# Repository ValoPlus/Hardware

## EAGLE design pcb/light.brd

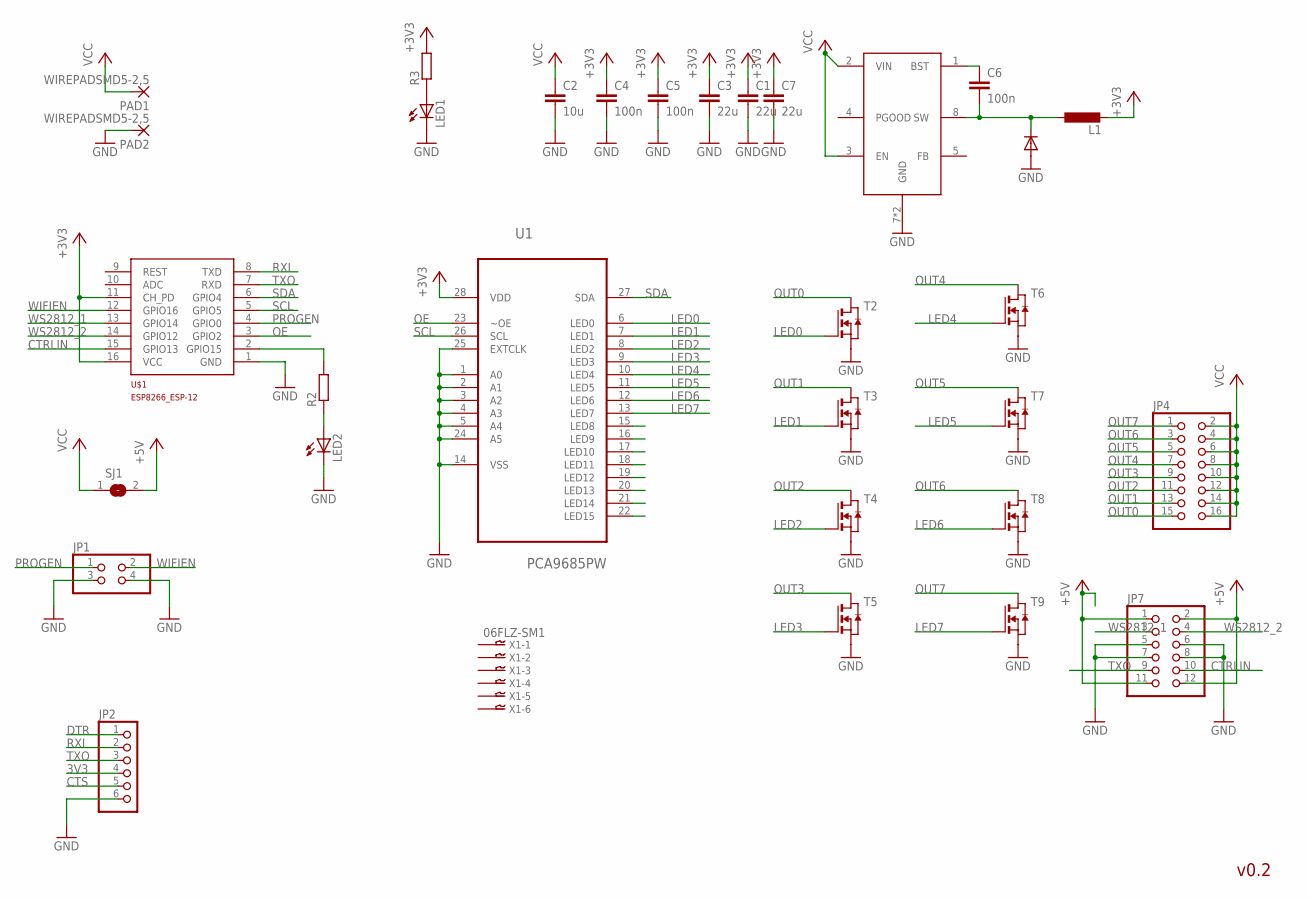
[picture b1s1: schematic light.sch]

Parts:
C1, C3, C7: 22u; C0805K
C2: 10u; C0805K
C4, C5, C6: 100n; C0603K
JP1: PINHD-2X2; 2X02
JP2: PINHD-1X6; 1X06
JP4: PINHD-2X8; 2X08
JP7: PINHD-2X6; 2X06
L1: L-EUL5650M; L5650M
LED1, LED2: LEDSML0603; SML0603
PAD1, PAD2: WIREPADSMD5-2,5; 5-2,5
R2, R3: R-EU_R0603; R0603
SJ1: SJ
T2, T3, T4, T5, T6, T7, T8, T9: NMOSSOT23; SOT-23
U1: PCA9685PW; SOP65P640X110-28N
U$1: ESP8266_ESP-12; ESP8266-ESP12
U$2: ADP2302; SOIC8G-1.27-5X4MM
U$3: SSB43L; DO-214AA
X1: 06FLZ-SM1; 6FLZ-SM

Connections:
3V3: JP2.4
+3V3: C1.1, C3.1, C4.1, C5.1, C7.1, L1.2, R3.2, U1.28 (VDD), U$1.11 (CH_PD), U$1.16 (VCC)
+5V: JP7.1, JP7.2, JP7.11, JP7.12, SJ1.2
CTRLIN: JP7.10, U$1.15 (GPIO13)
CTS: JP2.5
DTR: JP2.1
GND: C1.2, C2.2, C3.2, C4.2, C5.2, C7.2, JP1.3, JP1.4, JP2.6, JP7.5, JP7.6, JP7.7, JP7.8, LED1.C, LED2.C, PAD2.1, T2.2 (S), T3.2 (S), T4.2 (S), T5.2 (S), T6.2 (S), T7.2 (S), T8.2 (S), T9.2 (S), U1.1 (A0), U1.2 (A1), U1.3 (A2), U1.4 (A3), U1.5 (A4), U1.14 (VSS), U1.24 (A5), U1.25 (EXTCLK), U$1.1 (GND), U$2.7 (GND), U$2.PAD (GND), U$3.+ (A)
LED0: T2.3 (G), U1.6 (LED0)
LED1: T3.3 (G), U1.7 (LED1)
LED2: T4.3 (G), U1.8 (LED2)
LED3: T5.3 (G), U1.9 (LED3)
LED4: T6.3 (G), U1.10 (LED4)
LED5: T7.3 (G), U1.11 (LED5)
LED6: T8.3 (G), U1.12 (LED6)
LED7: T9.3 (G), U1.13 (LED7)
unnamed: LED1.A, R3.1
unnamed: LED2.A, R2.1
unnamed: R2.2, U$1.2 (GPIO15)
unnamed: C6.1, U$2.1 (BST)
unnamed: C6.2, L1.1, U$2.8 (SW), U$3.- (C)
OE: U1.23 (~OE), U$1.3 (GPIO2)
OUT0: JP4.15, T2.1 (D)
OUT1: JP4.13, T3.1 (D)
OUT2: JP4.11, T4.1 (D)
OUT3: JP4.9, T5.1 (D)
OUT4: JP4.7, T6.1 (D)
OUT5: JP4.5, T7.1 (D)
OUT6: JP4.3, T8.1 (D)
OUT7: JP4.1, T9.1 (D)
PROGEN: JP1.1, U$1.4 (GPIO0)
RXI: JP2.2, U$1.8 (TXD)
SCL: U1.26 (SCL), U$1.5 (GPIO5)
SDA: U1.27 (SDA), U$1.6 (GPIO4)
TXO: JP2.3, JP7.9, U$1.7 (RXD)
VCC: C2.1, JP4.2, JP4.4, JP4.6, JP4.8, JP4.10, JP4.12, JP4.14, JP4.16, PAD1.1, SJ1.1, U$2.2 (VIN), U$2.3 (EN)
WIFIEN: JP1.2, U$1.12 (GPIO16)
WS2812_1: JP7.3, U$1.13 (GPIO14)
WS2812_2: JP7.4, U$1.14 (GPIO12)

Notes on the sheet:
v0.2

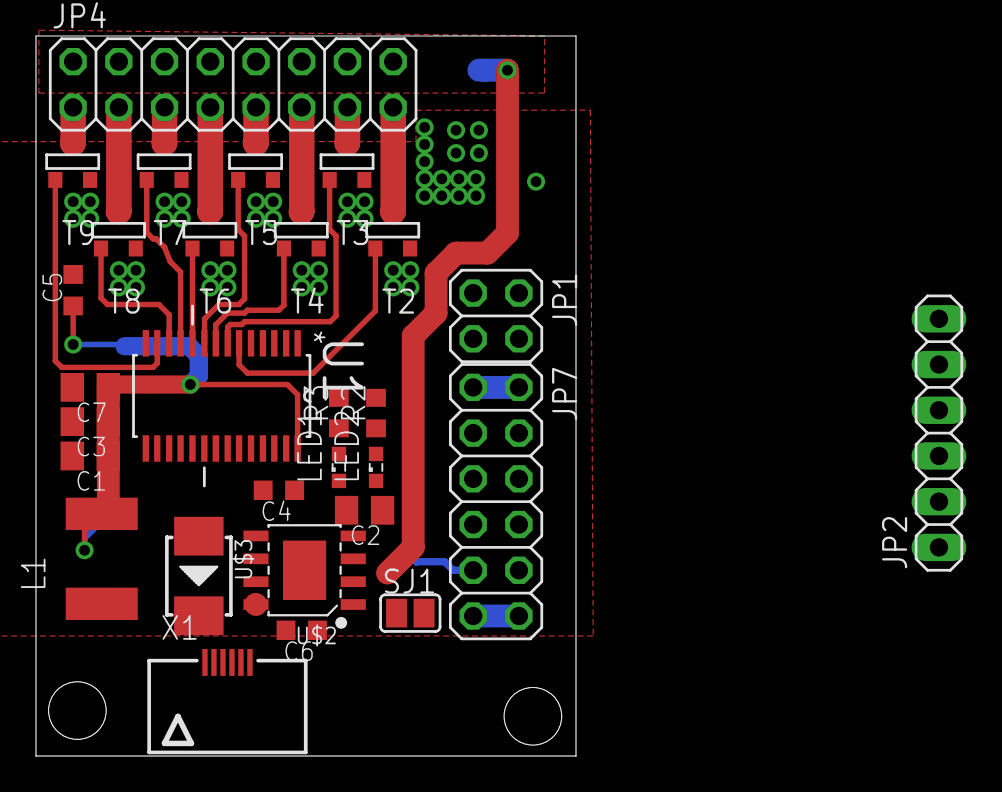
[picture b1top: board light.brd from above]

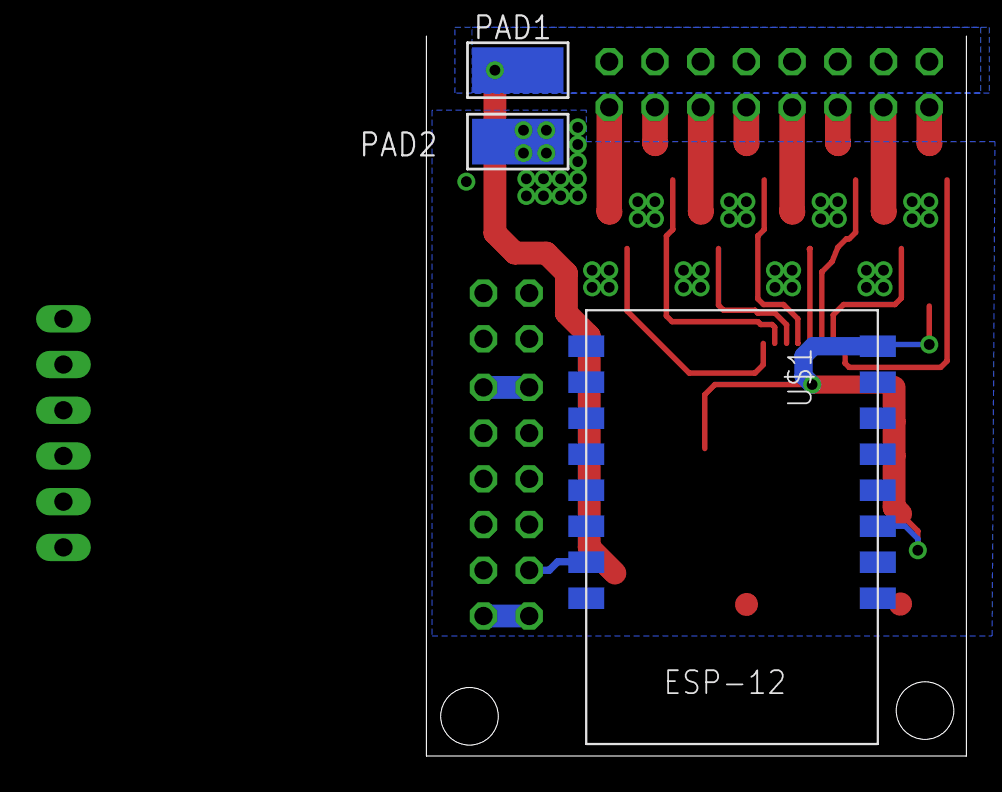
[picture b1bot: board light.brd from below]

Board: 2 copper layers, 30.0 x 40.0 mm, 32 parts (3 on the bottom side), 35 nets.

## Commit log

2016-05-19 Disabled firmware upload on build
2016-05-23 Update to newest API changes
2016-05-23 Removed old debugging code
2016-08-29 RestHttpServer
2016-08-29 temp commit
2016-08-29 removed linkedlist
2016-08-29 fixed linkedlist submodule
2016-08-30 Renamed domain folder
2016-09-25 - fix imports - add PersistentElement - add first Idea of PersistentService
